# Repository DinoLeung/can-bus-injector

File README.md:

# CAN Pulse

## Overview

A simple ESP32-based device that listens to and forwards CAN bus data from the 2022+ Toyota GR86 / Subaru BRZ (ZN8/ZD8).
The goal is to make CAN bus data available in [RaceChrono](https://racechrono.com).
It taps into the ASC unit (the “GazooKazoo”), which reads CAN data to produce fake engine noise. Many owners leave it unplugged anyway, we repurpose the data stream from there.

## Motivation

RaceChrono supports [DIY BLE CAN devices](https://github.com/aollin/racechrono-ble-diy-device), which opens the door to building a fully custom telemetry pipeline. Instead of relying on off-the-shelf hardware, this project aims to create a lightweight, purpose-built device that integrates cleanly with the car and exposes exactly the data needed.

It’s also a practical exercise in understanding the vehicle’s CAN network and building something that is both functional and extensible, rather than a black box.

## Roadmap

### Current Status

The basic firmware is complete and functional:
- CAN frames are read from the vehicle bus.
- Data is cached and filtered.
- Frames are forwarded over BLE using the RaceChrono DIY device protocol.

This means the device is already usable for real-time telemetry in RaceChrono.

### Next Step: High-Rate GPS Integration

The next major milestone is adding high-frequency GPS data support using the [ASL GPS bolt-on](https://wiki.autosportlabs.com/Gps-bolt-on)

Planned capabilities:
- Integrate GPS data alongside CAN telemetry.
- Support higher update rates than typical phone-based GPS.
- Improve lap timing accuracy and track position fidelity.

Longer term, this will allow the device to act as a complete standalone telemetry unit, rather than relying on the phone for positioning data.

## Hardware

### [ASL ESP-CAN-X2](https://wiki.autosportlabs.com/ESP32-CAN-X2)
### [ASL Gps-bolt-on](https://wiki.autosportlabs.com/Gps-bolt-on)

## References

This project is heavily based on reverse engineering work documented by the community, in particular:
- https://github.com/timurrrr/ft86/blob/main/can_bus/gen2.md

That document provides a detailed breakdown of the Gen2 GR86/BRZ CAN bus signals and effectively serves as the foundation for this project. It guided the identification of useful frames, signal meanings, and overall approach to decoding and forwarding data.

Without that work, building a usable and accurate telemetry pipeline would be significantly more time-consuming.

## Oil Pressure Oil Temperature Bolt-on

### Status

Abandon for now or at least deprioritised, due to lack of PCB design skills.

<details>

<summary>details</summary>

### Motivation

The factory setup leaves much to be desired:
- The gauge cluster on BRZ lacks a proper, high-resolution oil temperature gauge.
- Oil pressure data is absent.

This project aims to fill that gap by:
- Forwarding CAN data from the ASC (Active Sound Control) unit to a new CAN output.
- Reading engine oil pressure using a Bosch analog fluid pressure sensor (0 to 10 bar).
- Reading engine oil temperature using a Bosch analog fluid temperature sensor (-40 to 150 °C).
- Injecting that data into the new CAN bus stream so that digital dashboards and logging tools (e.g. RaceChrono) can display it.

Accurate oil pressure monitoring is critical in performance and track environments — especially given the FA24 platform’s known vulnerability to oil starvation during high-G right-hand turns.

### Features

- Dual-CAN forwarding: Reads from CAN1 (TWAI), writes to CAN2 (MCP2515).
- Sensor integration: Adds real-time oil pressure and temperature data (40Hz sampling rate, 20Hz update rate).
- Plug-and-play install: Designed to interface cleanly with the ASC connector and ESP32.

### Hardware

#### [Custom ASL ESP32-CAN-X2 Bolt-on](./bolt-on-bosch-pst-f-1/)
#### [Bosch Pressure Sensor Combined PST-F 1](https://www.bosch-motorsport.com/content/downloads/Raceparts/en-GB/54249355.html)

</details>

## License

- **Firmware** (ESP32 code): [GPLv3](./LICENSE)
- **Hardware design** (schematics, PCB layout): [CERN-OHL-S v2](./bolt-on-bosch-pst-f-1/LICENSE)

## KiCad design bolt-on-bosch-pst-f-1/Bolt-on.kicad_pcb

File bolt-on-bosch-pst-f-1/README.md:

# PST-F1 Bolt-On Daughter Board for ESP32-CAN-X2

A small daughter-board that lets you easily attach a Bosch PST-F1 combined pressure + temperature sensor to the AutosportLabs ESP32-CAN-X2.

## Overview

This daughter-board provides ESP32-CAN-X2 an interface for the Bosch PST-F1 combined pressure and temperature sensor (0–10 bar pressure + NTC temperature). It uses a 4-pin JST connector for sensor inputs. The board also passes through CAN2 signals from the ESP32-CAN-X2.

## Features

- **PST-F1 support**: 4-pin input (5 V, PRESS_SIG, TEMP_SIG, GND)
- **Voltage scaling & protection** on both sensor outputs
- **0.1 µF decoupling** on analog rails
- **Pass-through** of CAN2 channel

## Hardware Requirements

- [AutosportLabs ESP32-CAN-X2](https://wiki.autosportlabs.com/ESP32-CAN-X2) board
- [Bosch PST-F1 combined pressure-temperature sensor](https://www.bosch-motorsport.com/content/downloads/Raceparts/en-GB/54249355.html)

## Pinout & Connections

| PST-F1 Pin | Signal       | Daughter-Board Net | ESP32-CAN-X2 Pin |
|:----------:|:-------------|:-------------------|:----------------:|
| 1          | +5 V Supply  | 5V                 | SV1-pin 15 (5 V) |
| 2          | PRESS_SIG    | PRESS_ADC          | SV2-pin 13 (GPIO)|
| 3          | TEMP_SIG     | TEMP_ADC           | SV2-pin 12 (GPIO)|
| 4          | GND          | GND                | SV1-pin 16 (GND) |

## Analog Signal Scaling/Divider

### Pressure (0–10 bar → 0.32–2.88 V ADC)

- At 0.5 V (@ 0 bar / 0 PSI) -> ADC ≈ 0.32 V
- At 4.5 V (@ 10 bar / 145 PSI) -> ADC ≈ 2.88 V

``` mermaid
flowchart LR
  PSTF1_P["PST-F1 Pressure Out<br/>0.5 V @ 0 bar – 4.5 V @ 10 bar"]
  PRESS_ADC["PRESS_ADC Node"]
  R_SER_PRESS["R_SER_PRESS<br/>220 Ω"]
  R_PRESS_TOP["R_PRESS_TOP<br/>5.6 kΩ"]
  R_PRESS_BOT["R_PRESS_BOT<br/>10 kΩ"]
  D1["D1<br/>BAT54C"]
  D2["D2<br/>BAT54A"]
  C1["C1 Filter Cap<br/>0.1 µF"]
  GND["GND"]
  VCC["3.3 V"]
  GPIO["GPIO 35"]

  PSTF1_P --- R_SER_PRESS --- R_PRESS_TOP --- PRESS_ADC
  VCC ---|cathode| D1
  D1 ---|anode| PRESS_ADC
  GND ---|anode| D2
  D2 ---|cathode| PRESS_ADC
  PRESS_ADC --- R_PRESS_BOT --- GND
  PRESS_ADC --- C1 --- GND
  PRESS_ADC --- GPIO
```

### Temperature (NTC 58.1 Ω-44.864 kΩ → 0.01–2.9 V ADC)

- At cold (44 kΩ) → ADC ≈ 2.9 V
- At hot (58 Ω) → ADC ≈ 0.01 V

``` mermaid
flowchart LR
  PSTF1_P["PST-F1 Temperature Out<br/>44 kΩ @ –40 °C - 58 Ω @ +150 °C"]
  R_SER_TEMP["R_SER_TEMP<br/>220 Ω"]
  R_TEMP_TOP["R_TEMP_TOP<br/>6.8 kΩ"]
  TEMP_ADC["TEMP_ADC Node"]
  D1["D1<br/>BAT54C"]
  D2["D2<br/>BAT54A"]
  C2["C2 Filter Cap<br/>0.1 µF"]
  GND["GND"]
  VCC["3.3 V"]
  GPIO["GPIO 36"]

  PSTF1_P --- R_SER_TEMP --- TEMP_ADC
  TEMP_ADC --- C2 --- GND
  TEMP_ADC --- R_TEMP_TOP --- VCC
  VCC ---|cathode| D1  ---|anode| TEMP_ADC
  GND ---|anode| D2
  D2 ---|cathode| TEMP_ADC
  TEMP_ADC --- GPIO
```

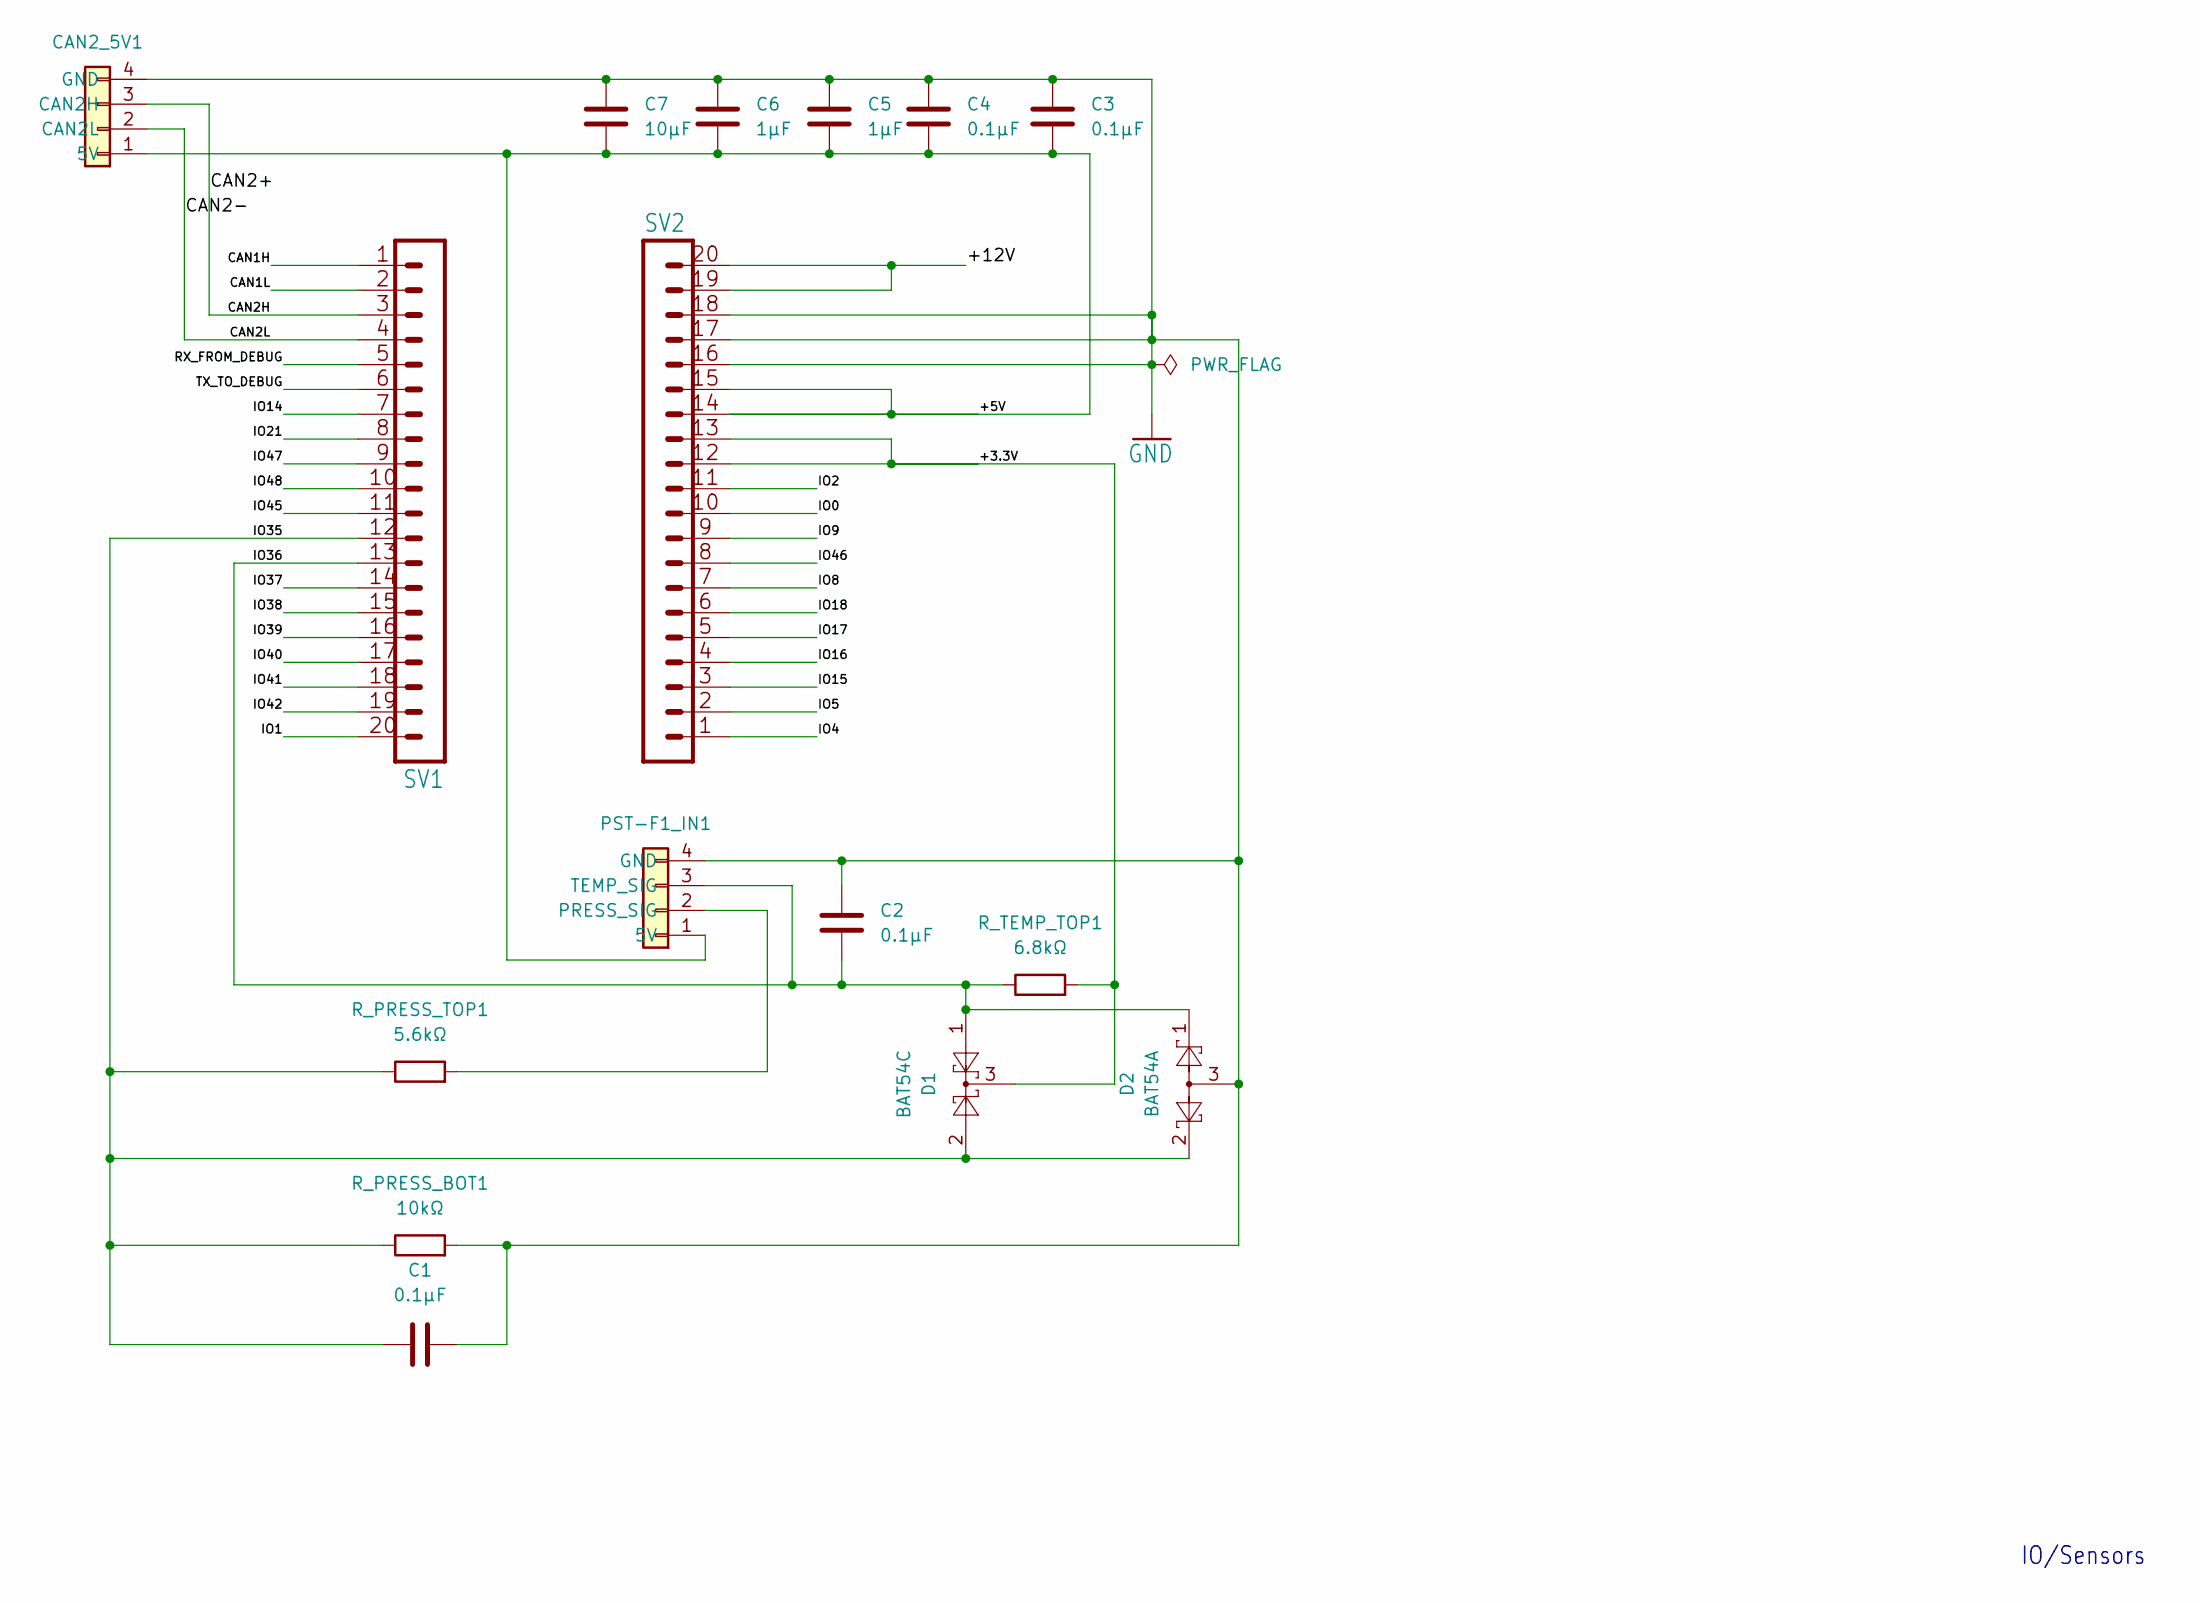
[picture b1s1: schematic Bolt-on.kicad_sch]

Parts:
C1, C2, C3, C4: ﻿0.1µF; C_0805_2012Metric_Pad1.18x1.45mm_HandSolder
C5, C6: 1µF; C_0805_2012Metric_Pad1.18x1.45mm_HandSolder
C7: 10µF; C_1206_3216Metric_Pad1.33x1.80mm_HandSolder
CAN2_5V1: Conn_01x04; JST_PH_S4B-PH-SM4-TB_1x04-1MP_P2.00mm_Horizontal
D1: BAT54C; SOT-23_Handsoldering
D2: BAT54A; TSOT-23_HandSoldering
PST-F1_IN1: Conn_01x04; JST_PH_S4B-PH-SM4-TB_1x04-1MP_P2.00mm_Horizontal
R_PRESS_BOT1: ﻿10kΩ; R_0805_2012Metric_Pad1.20x1.40mm_HandSolder
R_PRESS_TOP1: ﻿5.6kΩ; R_0805_2012Metric_Pad1.20x1.40mm_HandSolder
R_TEMP_TOP1: ﻿6.8kΩ; R_0805_2012Metric_Pad1.20x1.40mm_HandSolder
SV1, SV2: MA20-1L_162

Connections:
/+3.3V: D1.3, R_TEMP_TOP1.2, SV2.12, SV2.13
/+5V: C3.2, C4.2, C5.2, C6.2, C7.2, CAN2_5V1.1 (5V), PST-F1_IN1.1 (5V), SV2.14, SV2.15
/+12V: SV2.19, SV2.20
/CAN1H: SV1.1
/CAN1L: SV1.2
/CAN2+: CAN2_5V1.3 (CAN2H), SV1.3
/CAN2-: CAN2_5V1.2 (CAN2L), SV1.4
/IO0: SV2.10
/IO1: SV1.20
/IO2: SV2.11
/IO4: SV2.1
/IO5: SV2.2
/IO8: SV2.7
/IO9: SV2.9
/IO14: SV1.7
/IO15: SV2.3
/IO16: SV2.4
/IO17: SV2.5
/IO18: SV2.6
/IO21: SV1.8
/IO35: C1.2, D1.2, D2.2, R_PRESS_BOT1.1, R_PRESS_TOP1.1, SV1.12
/IO36: C2.2, D1.1, D2.1, PST-F1_IN1.3 (TEMP_SIG), R_TEMP_TOP1.1, SV1.13
/IO37: SV1.14
/IO38: SV1.15
/IO39: SV1.16
/IO40: SV1.17
/IO41: SV1.18
/IO42: SV1.19
/IO45: SV1.11
/IO46: SV2.8
/IO47: SV1.9
/IO48: SV1.10
/RX_FROM_DEBUG: SV1.5
/TX_TO_DEBUG: SV1.6
GND: C1.1, C2.1, C3.1, C4.1, C5.1, C6.1, C7.1, CAN2_5V1.4 (GND), D2.3, PST-F1_IN1.4 (GND), R_PRESS_BOT1.2, SV2.16, SV2.17, SV2.18
unnamed: PST-F1_IN1.2 (PRESS_SIG), R_PRESS_TOP1.2

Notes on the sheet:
IO/Sensors

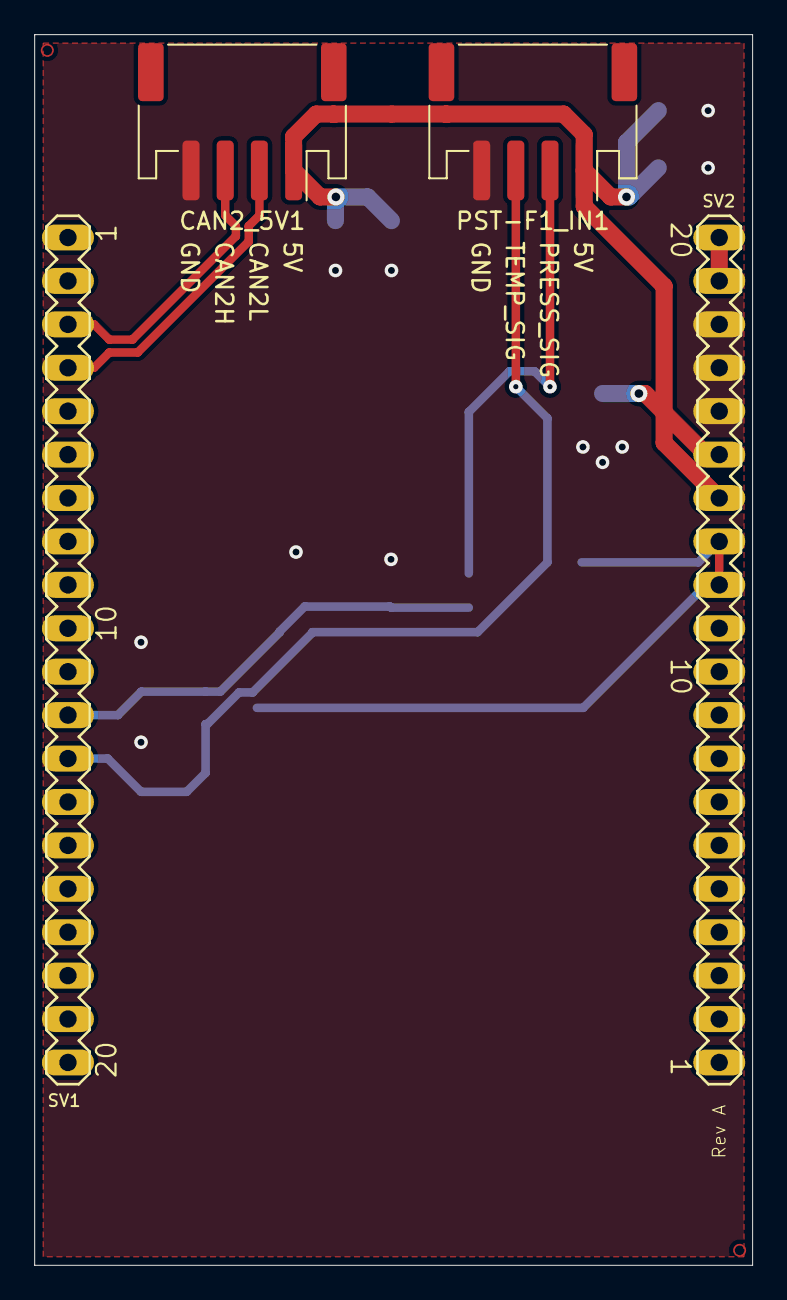
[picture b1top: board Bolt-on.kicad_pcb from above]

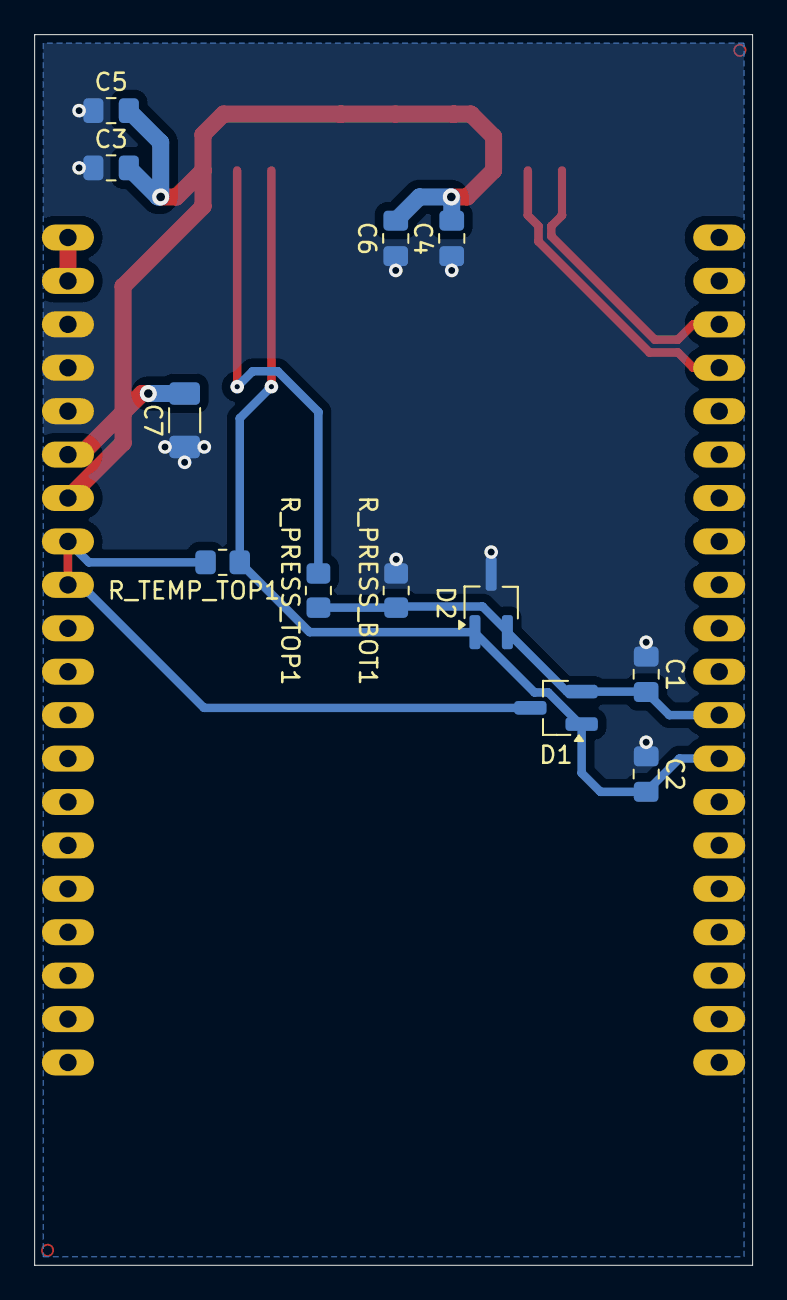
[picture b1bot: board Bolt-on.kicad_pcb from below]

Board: 2 copper layers, 42.0 x 72.0 mm, 16 parts (12 on the bottom side), 9 nets.

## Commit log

2025-07-14 project setup
2025-07-14 added basic readme
2025-07-14 added can init functions
2025-07-18 designing circuit board for bosch sensor
2025-07-25 designed circuit board for bosch sensor
2025-07-25 added labels to circuit board
2025-07-26 added readme for daughter board design
2025-07-26 cleanup board design
2025-07-27 implement basic can bus forwarder logic
2025-07-27 fix can1ReadTask param typo
2025-07-27 implemented sensor sample logic, and custom can writer logic
2025-07-28 add open source licenses
2025-07-28 move license files
2025-07-28 fixed typo in readme
2025-07-28 update temperature to signed int, update data sample tasks to 40hz
2025-07-28 code cleanup
2025-07-28 fix typo in readme
2025-07-29 add labels to jst pins
2025-07-30 split main into multiple files
2025-07-30 implement Steinhart–Hart equation for temps sensor
2025-08-03 redo pcb in kicad
2025-08-03 updated temperature sensor sampling task
2025-08-03 cleanup kicad design
2025-08-03 fixed resistors name
2025-08-03 added unit tests for conversions
2025-08-03 update doc blocks
2025-08-04 deleted temp file
2025-08-06 add copper pour to gnd and 5v
2025-08-06 swaped jst positions
2025-08-07 move python math script to sensor_math lib
2025-08-09 redo board layout
2025-08-10 update board layout
2025-08-10 added low diode for proper clamp
2025-09-29 pcb add ground copper pour on both sides
2025-10-09 pcb added tented gnd vias
2026-03-16 update readme, change of project direction
2026-03-16 setting up racechrono ble
2026-03-17 read can data from can 1
2026-03-18 add readme for bench can source
2026-03-18 cache can frames received
2026-03-18 cleanup
2026-03-18 fixed missing imports
2026-03-18 cleanup can frame cache
2026-03-19 implemented logic to take racechrono pid filter commands
2026-03-19 implemented allow all logic, implementing specific pid list
2026-03-20 reset filter request to deny all on disconnect
2026-03-20 cleanup and add doc blocks
2026-03-20 more doc blocks & symbol rename
2026-03-20 updated bench can device frames
2026-03-20 cleaup bench can device code
2026-03-20 adjust cache and queue sizes
2026-03-22 implementing gps data sampling
2026-03-22 gps ble characteristic
2026-03-23 implementing gps tasks

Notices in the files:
bolt-on-bosch-pst-f-1/Bolt-on.kicad_pcb:
Copyright 2023
